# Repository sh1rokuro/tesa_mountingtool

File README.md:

Tesa Mounting Tool – Orientation & Motion with BNO055

This project was developed as part of the Cross-Innovation-Class for Tesa. It serves as an interactive guidance system for the precise application of Tesa Powerstrips along a wall. The system detects orientation and motion deviations using the BNO055 sensor and visually indicates them via LEDs.

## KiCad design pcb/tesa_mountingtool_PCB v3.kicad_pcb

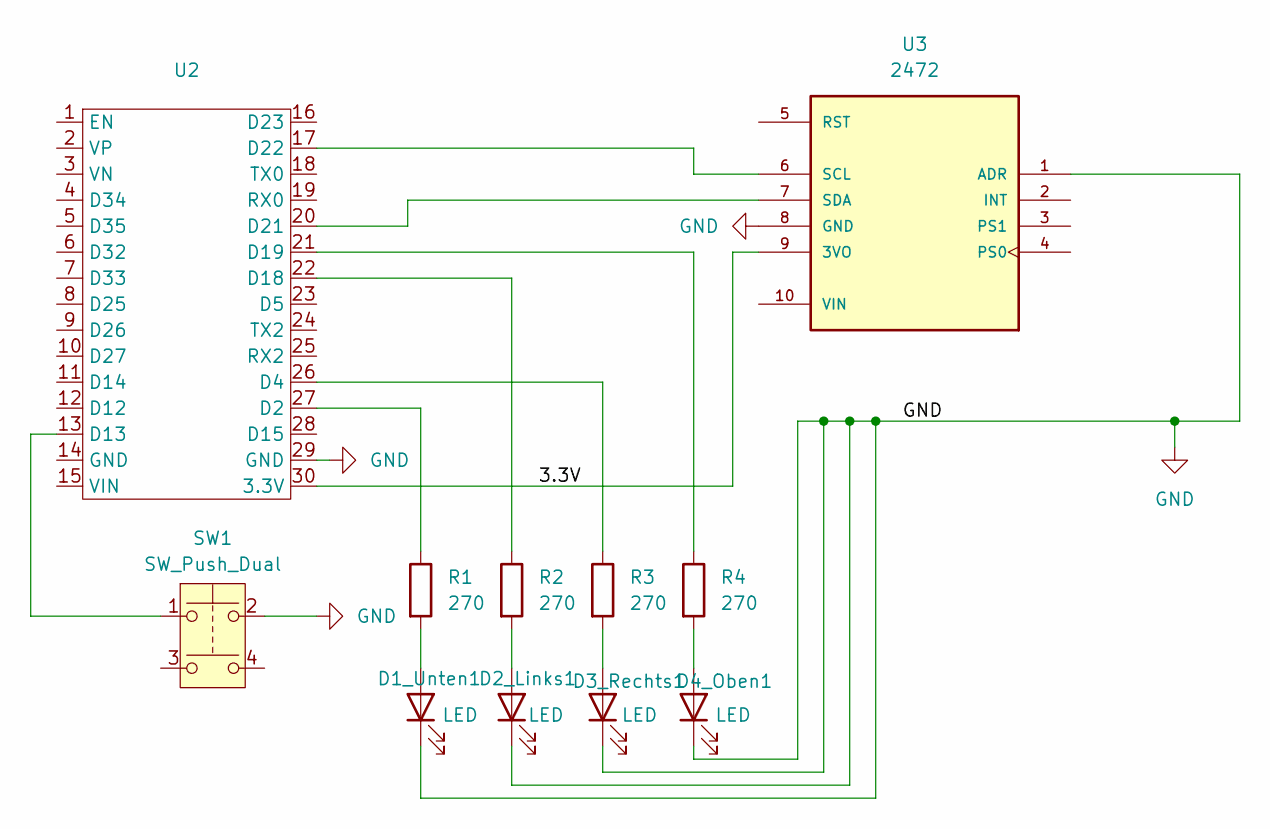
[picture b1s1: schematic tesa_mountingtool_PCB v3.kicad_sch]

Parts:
D1_Unten1, D2_Links1, D3_Rechts1, D4_Oben1: LED; LED_D3.0mm
R1, R2, R3, R4: 270; R_Axial_DIN0204_L3.6mm_D1.6mm_P2.54mm_Vertical
SW1: SW_Push_Dual; SW_SPST_Omron_B3F-40xx
U2: JOY-IT Node_MCU_ESP32
U3: 2472; MODULE_2472; PARTREV N/A

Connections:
/3.3V: U2.30 (3.3V), U3.9 (3VO)
GND: D1_Unten1.1 (K), D2_Links1.1 (K), D3_Rechts1.1 (K), D4_Oben1.1 (K), SW1.2, U2.29 (GND), U3.1 (ADR), U3.8 (GND)
unnamed: D1_Unten1.2 (A), R1.2
unnamed: D2_Links1.2 (A), R2.2
unnamed: D3_Rechts1.2 (A), R3.2
unnamed: D4_Oben1.2 (A), R4.2
unnamed: R1.1, U2.27 (D2)
unnamed: R3.1, U2.26 (D4)
unnamed: SW1.1, U2.13 (D13)
unnamed: R2.1, U2.22 (D18)
unnamed: R4.1, U2.21 (D19)
unnamed: U2.20 (D21), U3.7 (SDA)
unnamed: U2.17 (D22), U3.6 (SCL)

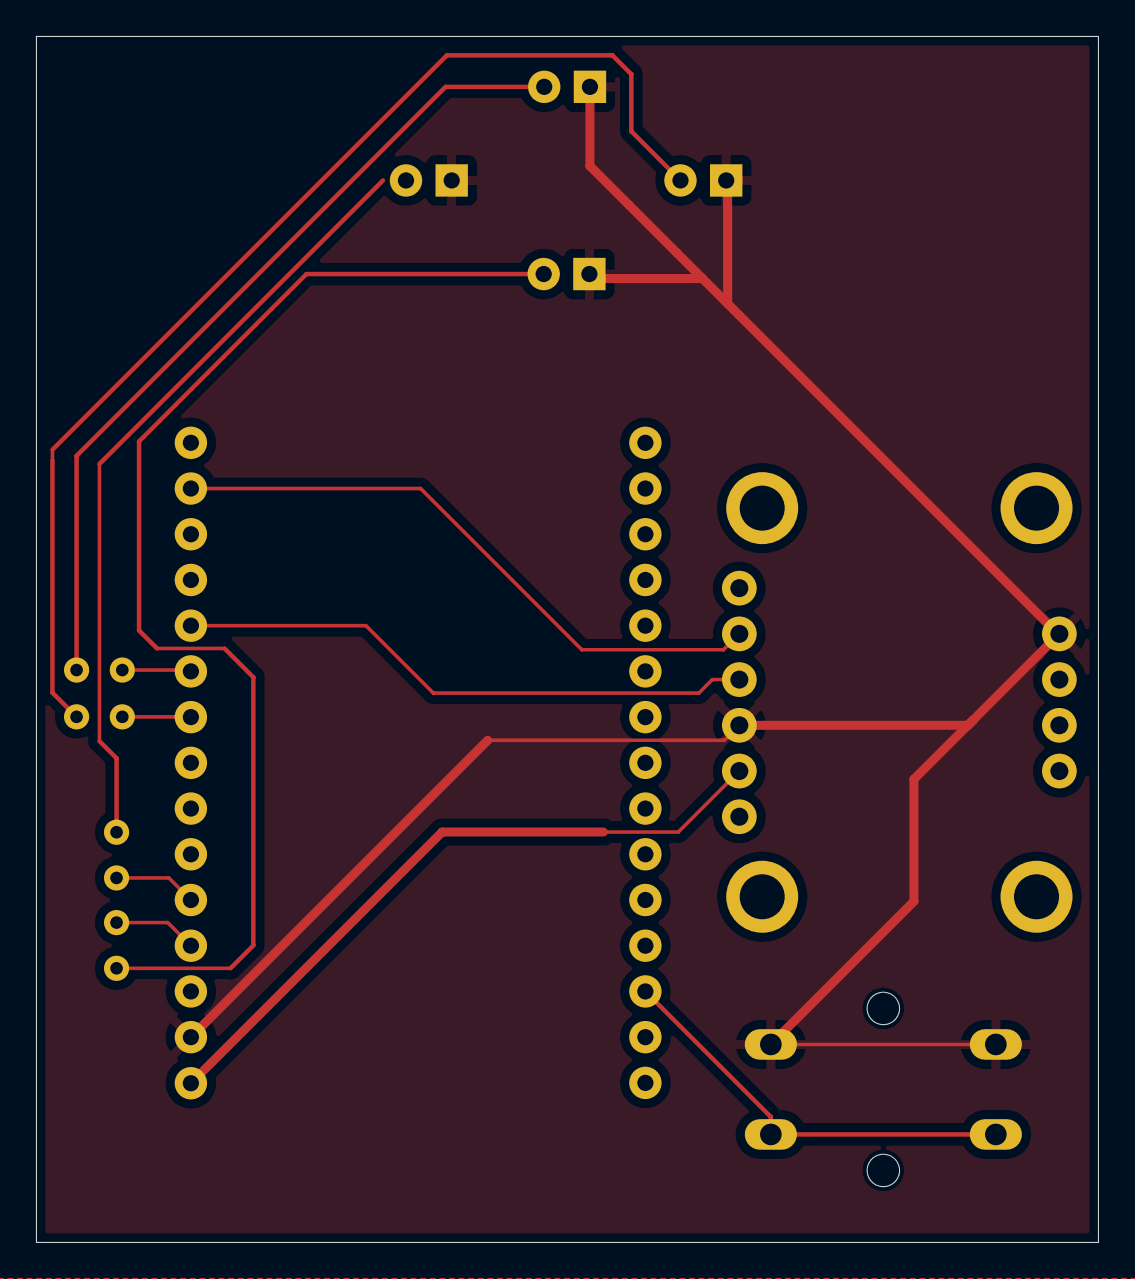
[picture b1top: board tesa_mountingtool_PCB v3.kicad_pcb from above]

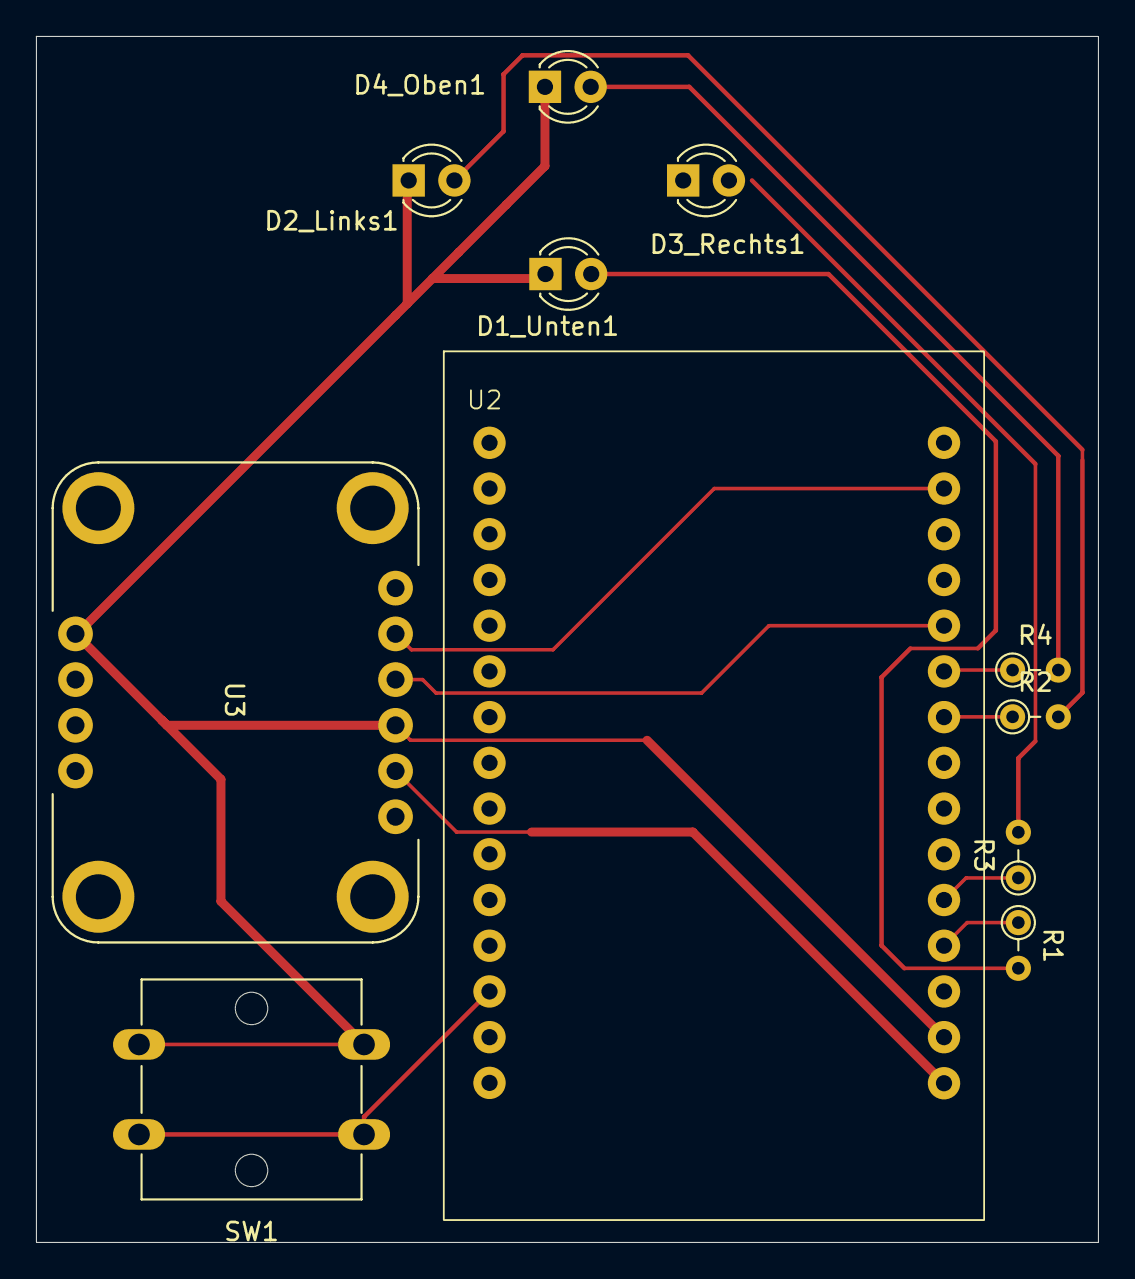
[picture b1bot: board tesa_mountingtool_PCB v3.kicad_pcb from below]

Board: 2 copper layers, 59.0 x 67.0 mm, 11 parts (11 on the bottom side), 13 nets.

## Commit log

2025-08-07 added finished software, pcb and case files
2025-08-07 add project documentation
